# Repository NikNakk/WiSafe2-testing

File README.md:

# WiSafe2 testing

Minimal ESP-IDF test harness for connecting a FireAngel WiSafe2 radio directly to an M5Stack AtomS3 Lite (ESP32-S3), without the Arduino Nano or 5 V/3.3 V level shifters used by the original bridge.

Based on the SPI/IRQ behaviour in [C19HOP/WiSafe2-to-HomeAssistant-Bridge](https://github.com/C19HOP/WiSafe2-to-HomeAssistant-Bridge).

## Important

This is experimental bench-test firmware. It is **not** part of the life-safety function of the FireAngel alarms and should not be relied on for alarm protection.

The WiSafe2 radio is the **SPI master** and the AtomS3 Lite is the **SPI slave**.

## Prototype wiring

The pin mapping below follows the radio connector nets traced from the original bridge PCB.

| WiSafe2 radio | AtomS3 Lite | Notes |
|---|---:|---|
| CS | GPIO8 | Radio -> Atom |
| IRQ | GPIO38 | Atom -> radio handshake |
| MOSI | GPIO6 | Radio -> Atom |
| SCK | GPIO5 | Radio -> Atom |
| MISO | GPIO7 | Atom -> radio |
| GND | GND | Common ground |
| 3V3 #1 | 3V3 | Supply |
| 3V3 #2 | 3V3 | Bridge to same 3.3 V supply |

The separate antenna connector has an ANT/RF pin and GND. For the prototype, connect the antenna as in the original bridge design and keep its ground common with the Atom/radio ground.

Do **not** connect the radio to 5 V logic. The AtomS3 Lite GPIO and the radio side of the original bridge are 3.3 V.

## What the test does

1. Configures the ESP32-S3 as an SPI slave.
2. Waits 5 seconds for the radio to stabilise, matching the original Nano firmware.
3. Sends the original init command byte-by-byte using the IRQ handshake:

   `D3 19 50 00 7E`

4. Waits for the expected response:

   `46 7E`

5. Queries the radio's pairing state with `D3 03 7E`.
6. If it is unpaired, reproduces the original bridge's pairing sequence:

   - sends `D3 12 01 7E`
   - requires `46 7E` followed by `41 7E`
   - announces the bridge identity as pseudo-device `A5 B8 13`, model `11 03`
   - opens a 21-second window in which you press the other FireAngel device's
     physical test/pair button
   - queries the pairing state again and reports the result

7. Enters raw receive mode and prints bytes/packets ending in `7E`.

The first goal is simply to establish whether ESP-IDF's SPI-slave driver can reproduce the timing expected by the WiSafe2 radio.

## Build and flash

Install a current ESP-IDF release, then from the repository root:

```bash
idf.py set-target esp32s3
idf.py build
idf.py -p /dev/ttyACM0 flash monitor
```

The serial port will vary by OS. On macOS it will normally appear under `/dev/cu.*`; run `ls /dev/cu.*` to identify it.

Exit the ESP-IDF monitor with `Ctrl+]`.

## ESPHome prototype

The repository also contains a local ESPHome external component in
`components/wisafe2`. It uses ESP-IDF's SPI-slave driver directly; do not add an
ESPHome `spi:` block because the WiSafe2 radio, rather than the AtomS3, is the
SPI master.

Copy `secrets.yaml.example` to `secrets.yaml`, enter the Wi-Fi and MQTT broker
credentials, and then compile or flash with:

```bash
esphome compile wisafe2.yaml
esphome run wisafe2.yaml
```

The ESPHome component publishes `Radio Initialized`, `Last Packet` and decoded
last-device diagnostics through the native API. A dedicated FreeRTOS task owns
the timing-sensitive SPI operations.

Each newly heard detector ID is stored in flash and advertised with retained
Home Assistant MQTT discovery messages. Home Assistant creates one device per
detector, containing alarm, low-battery, base-problem, model, last-event,
last-test result, last-test timestamp, raw-frame and remote-radio diagnostic
entities, including whether each retained detector is present in the latest
network SID map. Live `71` status frames additionally expose calibrated,
generic device-fault, on-base, detector-battery-fault, AC-failure and
radio-module-battery-fault states, plus the complete raw status byte. The bridge
walks the radio's SID map to identify paired detectors and also reacts
immediately when the radio announces a newly paired SID. Each detector also
exposes Home Assistant device triggers for alarm
detected, alarm cleared, physical test passed and physical test failed. These
events are not retained, so reconnecting Home Assistant or the broker cannot
replay an old alarm or test as a new trigger. Alarm
state remains unknown until live alarm-on (`50`) or alarm-off (`51`) traffic is
received because the diagnostic query cannot report an alarm already in
progress. The optional `refresh_detectors` button queries diagnostic state from
all known detectors on demand, first reconciling the radio's current SID map.
This remote diagnostic query is deliberately not scheduled periodically to
avoid unnecessary radio traffic and battery use;
only the bridge diagnostic and SID map are polled every 60 seconds. Unused
detector capacity is not advertised. The default inventory
limit is 16 and can be changed with `max_detectors` up to 32.
Discovery and state are republished after an MQTT reconnect.

Detector identity, model, type and SID are persisted in ESP flash, as are the
last physical-test result and timestamp. Live alarm, base, fault, membership and
remote-diagnostic values are not duplicated into flash: their MQTT state is
already retained by the broker and their history belongs in Home Assistant's
recorder. After a reboot, the component republishes discovery without
immediately replacing the retained snapshot. As fresh SID-map or diagnostic
traffic is published, fields not yet observed during that boot may become
unknown rather than being presented as newly measured state. Network membership
is refreshed from the SID map. This limits flash writes and makes the boundary
between last-known and currently observed data explicit.

Remote diagnostics expose the two battery readings and `Remote diagnostic
flags` exactly as raw values. They do not contain an established on-base field,
and neither reference implementation documents reliable thresholds that turn
the battery bytes into an OK/low state. Consequently, `Base` and `Battery`
remain unknown until a live `71` status packet supplies those states. Treating
zero remote diagnostic flags as proof that both states are OK would hide genuine
faults if the flags have a different meaning on another detector model. The two
raw battery readings, raw RSSI and radio fault count are published as
measurement sensors so Home Assistant records long-term statistics and can
graph their history.

The YAML deliberately sets ESPHome's ordinary MQTT entity discovery to false:
the bridge diagnostics arrive through the native API, while only the dynamic
detector devices use MQTT discovery. `log_topic` is also disabled to keep radio
diagnostic logs off MQTT. On ESP-IDF, `idf_send_async` keeps broker I/O on a
separate task so a slow MQTT publish cannot block ESPHome's main loop while a
detector diagnostic packet is being processed. The component also processes
radio events in bounded batches, yielding between bursts without affecting the
dedicated SPI task.

### Suggested Home Assistant alarm card

With the custom
[auto-entities](https://github.com/thomasloven/lovelace-auto-entities) and
[Mushroom](https://github.com/piitaya/lovelace-mushroom) cards installed, the
following dashboard card automatically adds one row for every detector exposed
by the bridge. It selects the detector's `Alarm` entity and obtains its
`Battery`, `Base`, `Last test result` and `Last test` entities from the same
Home Assistant device:

```yaml
type: custom:auto-entities
card:
  type: vertical-stack
card_param: cards
filter:
  template: >-
    {% set cards = namespace(items=[]) %}
    {% set alarm_classes = ['smoke', 'heat', 'carbon_monoxide'] %}
    {% for alarm in states.binary_sensor %}
      {% set dev = device_id(alarm.entity_id) %}
      {% if dev
            and device_attr(dev, 'manufacturer') == 'FireAngel'
            and alarm.attributes.device_class in alarm_classes %}
        {% set ns = namespace(
          battery_low=false,
          problem=false,
          test_result='unknown',
          last_test='unknown'
        ) %}
        {% for e in device_entities(dev) %}
          {% if state_attr(e, 'device_class') == 'battery'
                and is_state(e, 'on') %}
            {% set ns.battery_low = true %}
          {% elif state_attr(e, 'device_class') == 'problem'
                  and is_state(e, 'on') %}
            {% set ns.problem = true %}
          {% elif e.endswith('_test_result') %}
            {% set ns.test_result = states(e) %}
          {% elif state_attr(e, 'device_class') == 'timestamp' %}
            {% set ns.last_test = states(e) %}
          {% endif %}
        {% endfor %}
        {% if is_state(alarm.entity_id, 'on') %}
          {% set status = 'ALARM' %}
          {% set color = 'red' %}
        {% elif ns.battery_low %}
          {% set status = 'Battery low' %}
          {% set color = 'amber' %}
        {% elif ns.problem %}
          {% set status = 'Detector problem' %}
          {% set color = 'amber' %}
        {% else %}
          {% set status = 'Normal' %}
          {% set color = 'green' %}
        {% endif %}
        {% if ns.last_test not in ['unknown', 'unavailable', 'none', ''] %}
          {% set tested = as_timestamp(ns.last_test)
            | timestamp_custom('%d %b %Y %H:%M', true) %}
          {% set secondary = status ~ ' · Last test ' ~ tested %}
          {% if ns.test_result not in ['unknown', 'unavailable', 'none', ''] %}
            {% set secondary = secondary ~ ' (' ~ ns.test_result ~ ')' %}
          {% endif %}
        {% else %}
          {% set secondary = status ~ ' · No test recorded' %}
        {% endif %}
        {% set card = {
          'type': 'custom:mushroom-template-card',
          'entity': alarm.entity_id,
          'primary': device_attr(dev, 'name_by_user')
            or device_attr(dev, 'name'),
          'secondary': secondary,
          'icon': 'mdi:fire-alert' if is_state(alarm.entity_id, 'on')
            else 'mdi:smoke-detector',
          'color': color,
          'tap_action': {
            'action': 'navigate',
            'navigation_path': '/config/devices/device/' ~ dev
          }
        } %}
        {% set cards.items = cards.items + [card] %}
      {% endif %}
    {% endfor %}
    {{ cards.items | to_json }}
sort:
  method: name
```

The template uses the manufacturer and alarm device-class metadata published by
the component, so it does not depend on the ESPHome node name or generated
entity IDs. It resolves each Home Assistant device-registry ID while generating
the cards, allowing a tap to navigate directly to that detector's device page.
The last test result and UTC timestamp are retained by the firmware and restored
from flash after a reboot. The dashboard formats the timestamp in Home
Assistant's local timezone. A physical test received before SNTP has
synchronized still records its result, but cannot be assigned a reliable
timestamp.

### Notification blueprints

The same live alarm and physical-test traffic is also available through each
detector's device triggers in Home Assistant's automation editor. The blueprints
below remain useful when one automation should automatically include every
current and future FireAngel detector.

#### Real alarm notifications

The repository includes a Home Assistant automation blueprint for notifying on
real smoke, heat or carbon-monoxide alarms:

[FireAngel WiSafe2 real alarm notification](blueprints/automation/fireangel_wisafe2_alarm_notification.yaml)

It automatically covers detectors discovered after the automation is created.
A server-side `state_changed` trigger selects FireAngel alarm binary sensors by
manufacturer and device class, so renamed entities and the frontend registry
cache do not affect it. Only a transition of the detector's `Alarm` entity to
`on` is actionable; physical and remote test packets leave that entity off and
do not trigger notifications.

To install it, copy the blueprint to
`config/blueprints/automation/fireangel_wisafe2/` in Home Assistant, reload
automation blueprints, and create an automation from it. Its action selector can
send mobile-app notifications, persistent notifications, announcements or any
other Home Assistant action. Notification templates can use:

- `alarm_entity` and `alarm_entity_name`
- `alarm_device_id` and `alarm_device_name`
- `alarm_device_class` and the human-readable `alarm_type`
- `alarm_area_name` and `alarm_time`

The default action creates a persistent Home Assistant notification. Replace or
extend it when creating the automation to choose the desired recipients and
message.

#### Detector test notifications

A companion blueprint runs actions whenever a detector reports a new physical
test result:

[FireAngel WiSafe2 detector test notification](blueprints/automation/fireangel_wisafe2_test_notification.yaml)

It triggers from the persisted `Last test` timestamp rather than the PASS/FAIL
state, so two consecutive tests with the same result are both detected. A short,
configurable delay lets the companion result and event entities update before
the actions run. A five-minute freshness check prevents an old retained test
from generating a notification after a routine Home Assistant restart.
Templates can use:

- `test_device_id`, `test_device_name`, and `test_area_name`
- `test_alarm_device_class` and the human-readable `test_alarm_type`
- `test_result` and `test_event`
- `test_entity`, `test_timestamp`, and locally formatted `test_time`

Install this blueprint in the same Home Assistant blueprint directory described
above. It covers physical detector tests. The bridge's remote sound-test
buttons confirm radio transmission but do not generate per-detector test results,
so they cannot activate it.

### Alarm controls

The bridge device exposes native Home Assistant buttons for fire, CO and
combined interlink sound tests, fire/CO silence, checking the pairing state and
starting a 21-second pairing window. `Network Paired`, `Radio Command Running`
and `Last Radio Command` report command state and results. ESPHome device
availability, `Radio Initialized` and `Bridge Uptime` replace the original
serial heartbeat with explicit bridge and radio health reporting.

The component also polls the attached module's local diagnostic state and
network SID map every 60 seconds, and responds whenever the radio requests the
bridge identity with `41 7E`. These are local SPI management exchanges rather
than periodic per-detector queries or synthetic alarm-network heartbeats.
At the radio boundary, payload bytes `7E` and `7D` use WiSafe2 byte stuffing
(`7D 01` and `7D 02` respectively); the terminal `7E` remains unescaped. Frames
are restored to their logical bytes before decoding and diagnostic publishing.

The sound-test buttons confirm only that the donor radio accepted and
transmitted the request. WiSafe2 detectors do not return individual results for
a remotely initiated sound test. To exercise and record the self-test result of
each detector, press that detector's physical test button. Emergency simulation
is intentionally not exposed.

## Comparison with the reference implementations

This project draws on two independent, reverse-engineered implementations:
[C19HOP/WiSafe2-to-HomeAssistant-Bridge](https://github.com/C19HOP/WiSafe2-to-HomeAssistant-Bridge)
and [Tho85/ws2mqtt](https://github.com/Tho85/ws2mqtt). Neither is an official
WiSafe2 protocol specification, although C19HOP's repository includes
[captured debug output](https://github.com/C19HOP/WiSafe2-to-HomeAssistant-Bridge/blob/master/FireAngelProConnectedGateway/DeviceTest2.txt)
from FireAngel's own Connected Gateway firmware. Where the two implementations
disagree, that manufacturer-firmware evidence is preferred.

| Area | C19HOP bridge | ws2mqtt | This ESPHome component |
|---|---|---|---|
| Hardware and transport | Arduino Nano acting as the SPI slave, with a USB serial connection to Home Assistant. | Arduino/ATmega SPI-to-UART adapter plus a separate ESP32 MQTT gateway. | ESP32-S3 talks to the radio directly as an SPI slave and runs ESPHome, eliminating the intermediate microcontroller and serial protocol. |
| Detector inventory | Detector IDs are learned from received traffic and configured manually in the supplied Home Assistant templates. | Maintains a device database, walks the `D4 03` SID map, resolves unknown SIDs with `D3 06 <sid> 01`, and reacts to `D4 09` join notifications. | Uses the ws2mqtt-style SID discovery flow, persists the resulting inventory, and creates detector devices using MQTT discovery. |
| Remote diagnostics | Primarily derives detector state from unsolicited network traffic. | Supports `D3 06 <sid> 00` remote diagnostic requests, although its README recommends avoiding routine active queries to conserve detector batteries. | Queries a detector while discovering it and exposes an explicit **Refresh Detector Diagnostics** button. Remote requests are serialized and may take tens of seconds because the radio returns `C4`/`D4 06` asynchronously. It does not periodically poll individual detectors; only the attached radio and SID map are polled every 60 seconds. |
| `71` status flags | The original published analysis treats `04` as docked/on-base and `02` or `40` as low-battery indications. Its captured official-gateway log instead names bits `01` calibrated, `02` faulty, `04` on-base, `08` detector-battery fault, `10` AC failed and `20` radio-module-battery fault. | Exposes generic fault (`02`), docked (`04`), detector battery (`08`) and radio-module battery (`20`) binary sensors. | Uses all six names from the FireAngel gateway log. Separate binary sensors expose each meaning, `Battery` remains a compatibility OR of `08` and `20`, `Base` remains the inverse of `04`, and the raw byte preserves unnamed bits `40` and `80`. |
| Alarm state | Focuses on event reporting through serial/Home Assistant templates. | Handles live alarm-on and alarm-off traffic and deliberately starts alarm state as unknown because it cannot be queried. | Likewise changes alarm state only from live `50`/`51` events. Diagnostic polling never assumes that an alarm is off. |
| Reserved-byte framing | The available SPI analysis does not describe a separate byte-stuffing layer. | Explicitly maps payload `7E` to `7D 01` and payload `7D` to `7D 02`. | Applies the ws2mqtt mapping on every SPI transmit and receive path while leaving the final `7E` delimiter unescaped. |
| Inventory removal | Has no comparable persistent automatic database to reconcile. | Clears its device database when the attached radio reports the unpaired/reset SID state (`D2` SID `40`). | Deliberately retains previously discovered detectors. A per-detector `Network member` diagnostic shows whether each retained entry is present in the latest SID map, avoiding silent Home Assistant device deletion after a transient reset or radio replacement. |
| Trailing packet fields | Unknown trailing bytes are generally passed through or ignored. | Some receive structures label trailing bytes as SID and sequence metadata. | Accepts extended frames but reads only independently established offsets. The possible SID/sequence fields remain undecoded until captures confirm their meaning across packet types. |
| Command pacing | Timing follows the Nano firmware's blocking SPI/IRQ flow. | Enforces a minimum interval of approximately 500 ms between transmissions. | Enforces a 500 ms quiet interval after transmitted and received frames before issuing another command. This also accommodates asynchronous `C4` identity and `D4 06` status replies observed on real hardware. |
| Model catalogue | Documents the FP2620W2, FP1720W2, WST-630, W2-SVP-630 and W2-CO-10X devices used by that project. | Also reports testing with the ST-630-DE(P) and HT-630-EUT, and stores model numbers in manufacturer numeric order such as `08ED`. | Includes the C19HOP models plus ST-630-DE(P). Internal constants and raw entities retain packet-byte order (`ED08`, `7C04`) for compatibility; FireAngel's gateway displays those numeric models as `08ED`, `047C`. The HT-630-EUT remains identified by its reported device type until an explicit model ID is available. |
| Home Assistant model | Serial JSON plus user-maintained template sensors and commands. | MQTT discovery devices and gateway-level Home Assistant events. | ESPHome native bridge controls plus dynamically discovered per-detector MQTT entities, per-device alarm/test triggers and network-wide automation blueprints. `via_device` is intentionally omitted: the bridge belongs to ESPHome's native-API config entry while the detectors belong to MQTT, and linking across integrations would require a duplicate MQTT bridge device. |

The main open protocol questions are therefore the meaning of `71` bits `40`
and `80`, trailing SID/sequence bytes, and model IDs not yet seen in this
project's captures. These should be resolved with timestamped raw frames and,
where timing is involved, logic-analyser traces from real hardware.

## Tests

The radio packet decoder is platform-independent and has host-side coverage for
the observed detector status frames, tests, emergencies, silence, attached-radio
diagnostics, identity responses, battery/base flags, extended frames and
malformed input, including reserved-byte escaping. It also exercises the radio
transport state machine with a fake clock and SPI adapter, covering command
pacing, queue/acknowledgement order, timeouts, asynchronous responses and reset
recovery. `D2` is treated as a
diagnostic response from the attached radio rather than a missing-detector
event. Known packet types use minimum
lengths because observed variants carry trailing fields that are not yet
understood; decoding reads only the established fixed offsets and preserves the
complete raw frame for diagnostics. Run the tests without an ESP32 toolchain:

```bash
./tests/run_tests.sh
```

GitHub Actions runs the protocol tests, validates the ESPHome configuration and
compiles the complete firmware for every push and pull request. CI copies the
tracked placeholder values from `secrets.yaml.example`; real credentials remain
in the ignored `secrets.yaml` file and are never required by the workflow.

The host suite validates the transport's ordering and timeout decisions, but it
does not emulate ESP-IDF's SPI-slave driver or electrical timing. The 8 µs IRQ
pulse and the radio's occasional extra clocks still require bench testing with
the donor radio.

## Versioning

The firmware/project version is set in `esphome.project.version` in
`wisafe2.yaml`. The ESPHome version pinned in `.github/requirements-ci.txt` is
the CI build toolchain version, not the project version. Release changes are
recorded in `CHANGELOG.md`; future releases should also use annotated Git tags
such as `v0.2.0`.

## Expected log

If the radio handshake works, the important result is:

```text
INIT TX: D3 19 50 00 7E
...
INIT RX: 46 7E
*** INIT OK: received expected 46 7E ***
```

If the first TX byte times out, check power, common ground, IRQ/CS wiring and the pin mapping before changing the protocol code.

## Current limitations

The standalone test harness intentionally does not implement Wi-Fi, heartbeat,
alarm entities, test commands or silence commands. Its pairing flow remains an
automatic boot-time bench test. The ESPHome implementation provides
Wi-Fi/API/OTA, packet decoding, persistent MQTT-discovered detector devices and
the supported management commands. WiSafe2 does not provide a known remote
command that individually self-tests every detector and reports its result.

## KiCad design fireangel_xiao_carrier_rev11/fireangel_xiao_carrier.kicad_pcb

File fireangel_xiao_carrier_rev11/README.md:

# Rev 11 review fixes

This revision addresses review of the generated KiCad file itself.

## Fixed: explicit KiCad net table and numeric net codes

The board now contains an explicit top-level net table:

- 1 GND
- 2 +3V3
- 3 CS
- 4 IRQ
- 5 MOSI
- 6 SCK
- 7 MISO
- 8 ANT

Connected through-hole pads use `(net N "NAME")`, tracks/vias use `(net N)`,
and zones use `(net N) (net_name "NAME")`.

## Review comments about CS/IRQ short and dangling stubs

Those coordinates do **not** occur in the current Rev 10/Rev 11 board. They
appear to describe an older generated layout. The current routing was inspected
before this conversion and does not contain the cited `(15,31)`, `(15,35)`,
`(15,37.54)`, `(15,39)`, `(15,43)`, `(15,47)`, `(33,42.5)`, or `(7,51)` stubs.

There are no routing changes from Rev 10 in Rev 11; this revision changes only
the KiCad net representation.

Please open in KiCad 10.0.5 and run DRC again before fabrication.

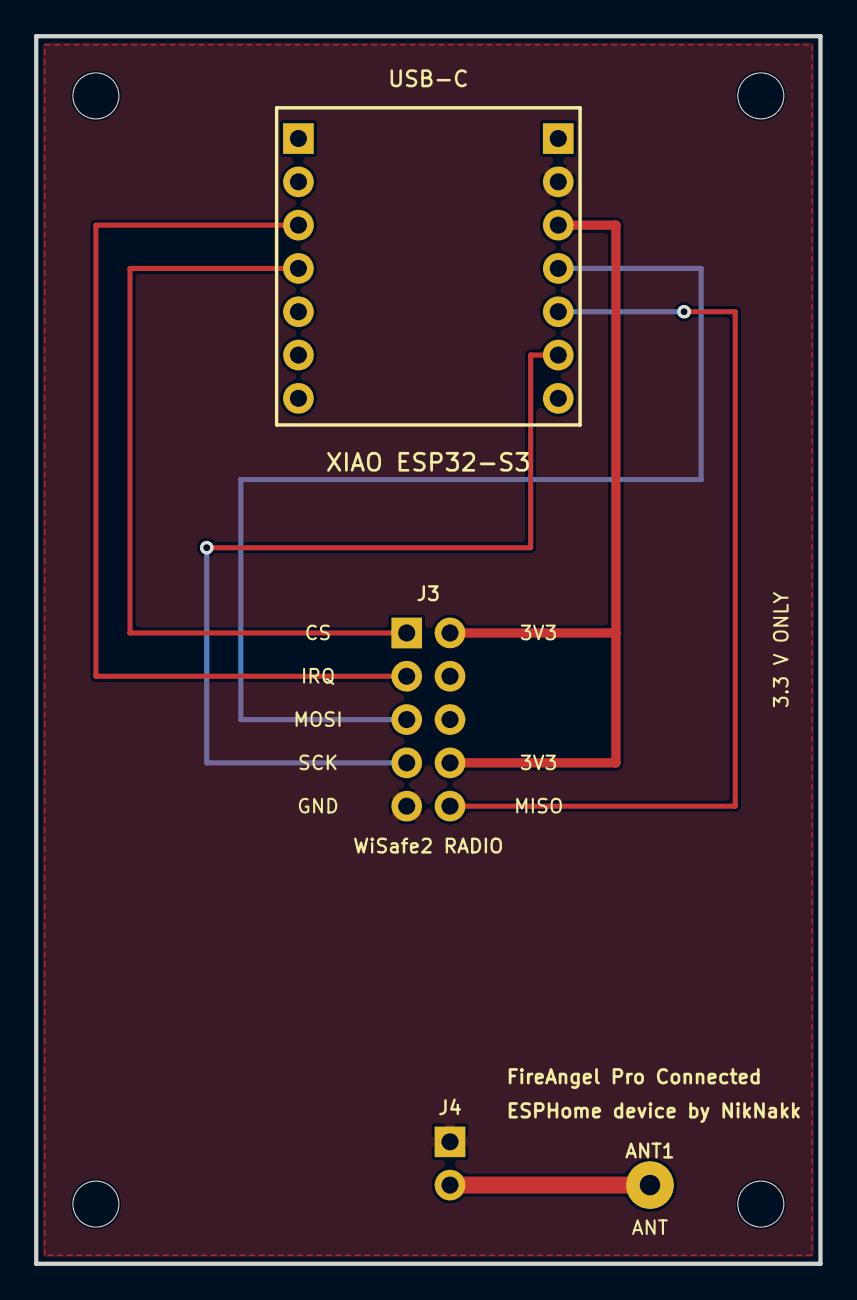
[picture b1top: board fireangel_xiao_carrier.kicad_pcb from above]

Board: 2 copper layers, 46.0 x 72.0 mm, 9 parts (0 on the bottom side), 8 nets.

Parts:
ANT1: Antenna_Wire_Pad
H1, H2, H3, H4: MountingHole_2.7mm_M2.5
J1: XIAO_Left_1x07
J2: XIAO_Right_1x07
J3: WiSafe2 RADIO; WiSafe2_2x05
J4: WiSafe2_ANT_1x02

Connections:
+3V3: J2.3, J3.6, J3.9
ANT: ANT1.1, J4.2
CS: J1.4, J3.1
GND: J2.2, J3.5, J4.1
IRQ: J1.3, J3.2
MISO: J2.5, J3.10
MOSI: J2.4, J3.3
SCK: J2.6, J3.4

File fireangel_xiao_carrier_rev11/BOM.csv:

Ref,Qty,Part,Notes
"J1,J2",2,1x7 2.54mm female socket,XIAO ESP32-S3
J3,1,2x5 2.54mm female socket,WiSafe2 radio
J4,1,1x2 2.54mm female socket,WiSafe2 ANT/GND
ANT1,1,large plated through-hole pad,~86 mm antenna wire
H1-H4,4,2.7mm mounting hole,M2.5 hardware
MODULE1,1,Seeed Studio XIAO ESP32-S3,plain version
